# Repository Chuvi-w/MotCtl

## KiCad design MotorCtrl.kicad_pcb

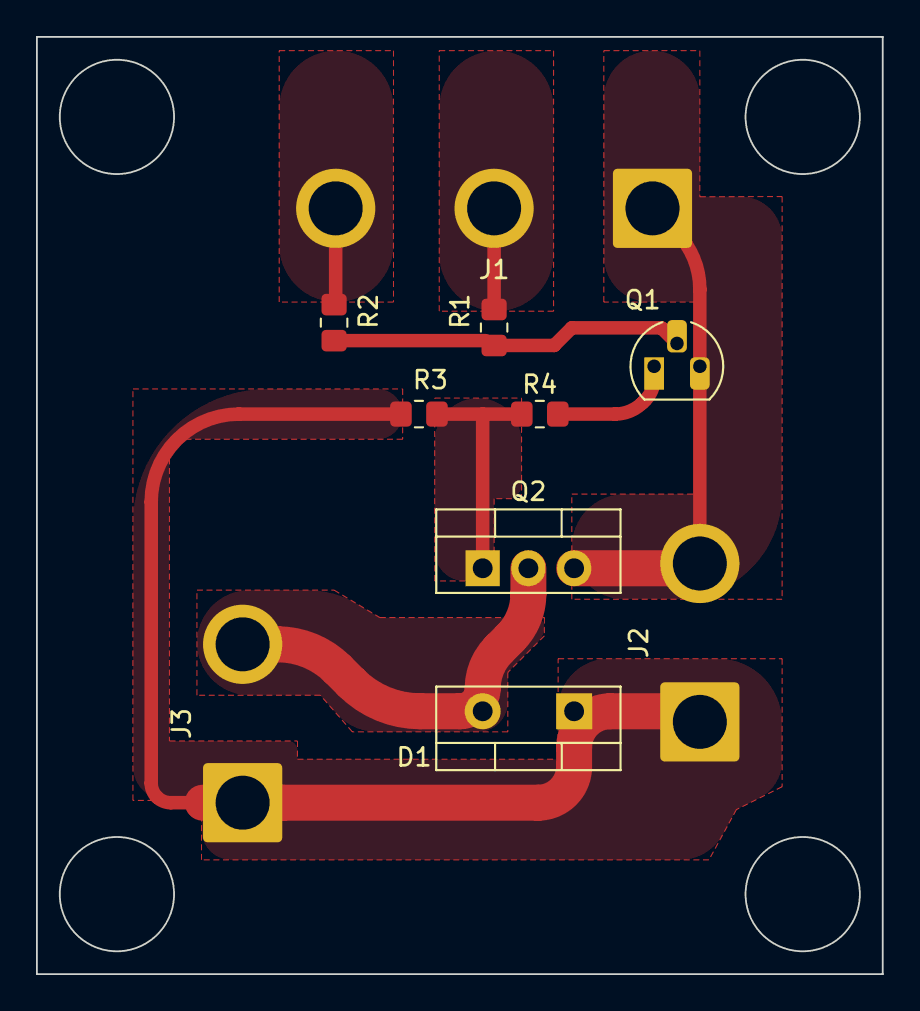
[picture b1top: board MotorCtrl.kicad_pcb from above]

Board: 2 copper layers, 47.0 x 52.1 mm, 10 parts (0 on the bottom side), 8 nets.

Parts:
D1: D; TO-220-2_Vertical
J1: Conn_01x03_Female; SolderWire-2.5sqmm_1x03_P8.8mm_D2.4mm_OD4.4mm
J2, J3: Conn_01x02_Female; SolderWire-2.5sqmm_1x02_P8.8mm_D2.4mm_OD4.4mm
Q1: BS108; TO-92_HandSolder
Q2: IRLB8721PBF; TO-220-3_Vertical
R1, R4: 200; R_0805_2012Metric_Pad1.20x1.40mm_HandSolder
R2, R3: 10K; R_0805_2012Metric_Pad1.20x1.40mm_HandSolder

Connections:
+5V: J1.3, R2.1
+12V: D1.1 (K), J2.1, J3.1, R3.1
GND: J1.1, J2.2, Q1.3 (S), Q2.3 (S)
unnamed: D1.2 (A), J3.2, Q2.2 (D)
unnamed: J1.2, R1.2
unnamed: Q1.1 (D), R4.2
unnamed: Q1.2 (G), R1.1, R2.2
unnamed: Q2.1 (G), R3.2, R4.1

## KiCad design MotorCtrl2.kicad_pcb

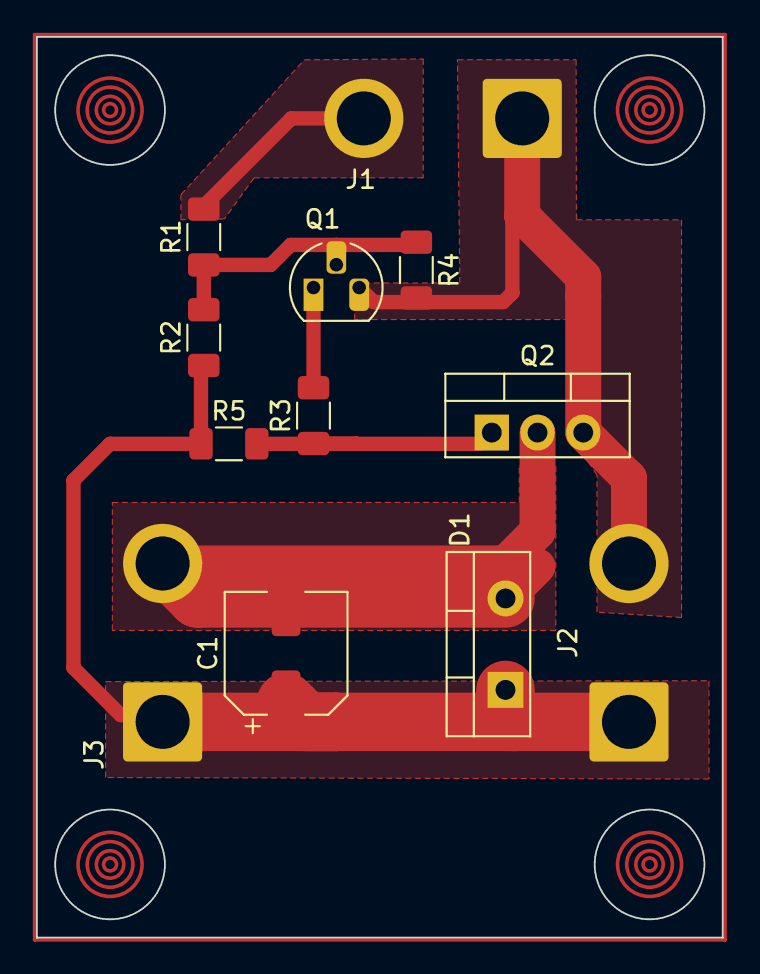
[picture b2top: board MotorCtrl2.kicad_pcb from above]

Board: 2 copper layers, 38.1 x 50.0 mm, 12 parts (0 on the bottom side), 7 nets.

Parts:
C1: C; CP_Elec_6.3x4.5
D1: D; TO-220-2_Vertical
J1, J2, J3: Conn_01x02_Female; SolderWire-2.5sqmm_1x02_P8.8mm_D2.4mm_OD4.4mm
Q1: BS108; TO-92_HandSolder
Q2: IRLB8721PBF; TO-220-3_Vertical
R1, R3: 200; R_1206_3216Metric_Pad1.30x1.75mm_HandSolder
R2: 12K; R_1206_3216Metric_Pad1.30x1.75mm_HandSolder
R4: 4,5K; R_1206_3216Metric_Pad1.30x1.75mm_HandSolder
R5: 10K; R_1206_3216Metric_Pad1.30x1.75mm_HandSolder

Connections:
+12V: C1.1, D1.1 (K), J2.1, J3.1, R2.1, R5.1
GND: J1.1, J2.2, Q1.3 (S), Q2.3 (S), R4.2
unnamed: C1.2, D1.2 (A), J3.2, Q2.2 (D)
unnamed: J1.2, R1.2
unnamed: Q1.1 (D), R3.2
unnamed: Q1.2 (G), R1.1, R2.2, R4.1
unnamed: Q2.1 (G), R3.1, R5.2

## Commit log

2022-12-27 init
2022-12-27 sch done
2022-12-27 zones
2022-12-27 round
2022-12-29 AddScatch
